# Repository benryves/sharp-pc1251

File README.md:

# Sharp PC-1251 & EC-125

This is a collection of example programs and tools for the Sharp PC-1251 and EC-125.

_**Disclaimer:** Except for the Audio Adapter, none of these files are my own. The original examples and documents are owned by Sharp and Pocket Tools is attributed below._

More information about this project can be found on my Retro website: [retro.engineer](https://retro.engineer/projects/2021-01-16_Sharp_PC-1251/)

## Audio-Adapter directory

This directory contains the designs for the audio adapter PCB which is for sale in my [Tindie shop](https://www.tindie.com/products/22618/). 

## Audio directory

This contains audio recordings of the original example programs provided on the EC-125 micro-cassette, as well as a Dutch game presumably made by a previous owner of my device.

These files can be played back to the PC-1251 using the EC-125 audio-in connection.

## Basic directory

These are the basic files converted from the above audio files using Pocket Tools (see below)

Files A09 and A11 encountered errors during decoding and might not be reliable.

## Manuals directory

User guides:

* Sharp PC-1250 user guide
* Sharp CE-125 user guide

Service guides:

* Sharp PC-1250 service manual
* Sharp CE-125 circuit diagrams (very minimal)

Related guides:

* Seiko MTP201 technical reference (Printer used in the CE-125)
* Sharp CE-126P service manual (contains the same printer as used in the CE-125)

## EC-125 modification

The EC-125 only has an audio input and no option for audio output. But since I don't own any other micro-cassette players I decided to make a temporary modification to allow me to capture the audio.

I soldered a wire to the amplifier IC. This is the positive output of the audio signal, I used the battery ground as ground without any issue:

## Pocket Tools for macOS.

These are MacOS X binaries for the Pocket Tools available on [https://www.peil-partner.de/ifhe.de/sharp](https://www.peil-partner.de/ifhe.de/sharp) compiled and tested on macOS Catalina

Original sources are also included

wav2bin
```
Usage: wav2bin [Options] SrcFile(.wav/tap/img) [DstFile(.typ)]
SrcFile           : WAVe file (PCM, normalized, recommended is mono 16-bit with
                    a minimum sample rate from 22050 Hz (PC-1500 only 11025 Hz)
                    to 48 kHz or original wave files made by Bin2Wav)
DstFile           : Destination file (BASIC-program text or Binary image file)
Options
-t, --type=TYPE   : Destination file type
                     bas  BASIC-program text file (default), sha  shc Transfile
                     img  Binary image file (BASIC program, machine code, data)
                     rsv  ReSerVe mode data (image),   tap  Emulator raw format
-p, --pc=NUMBER   : SHARP pocket computer, (for BASIC-program text,
                     is required for 1421, 1600 Mode 1, optionally for other)
-c, --cspeed=VALUE: Ratio of CPU frequency to original (use it with a modified
                     Pocket Computer, if speedup was switched on, 0.94 to 2.7)
-u, --utf8=TYPE   : Convert special characters (only for BASIC-program text)
                     no   to ASCII transcription with brackets [reversible]
                     (yes), BOM: to UTF-8,  2esc: Escape seq,  2dos: to DOS-US
                     2asc to ASCII transcription for later serial transfer
-w, --width=VALUE : Minimum width of line number (only for BASIC-program text)
  | VAL[:|;|,|.|!]   2 to 10 (default: 5_), indentation off: 0, =VAL; for (: )
-q, --quiet       : Quiet mode (No display output)    2nd use: -w space_level.
    --tap         : from emulator tap,  --img=OFFSET: Image (Src file no wave)
    --version     : Display version information  -e, --endmark : write end mark
    --help        : Display this, more:  --help=r:recoding FAQ, =l:level(debug)
```

bin2Wav

```
Usage: bin2wav [Options] SrcFile(.typ) [DstFile(.wav/tap)]
SrcFile          : Binary image file (usually created by BAS2IMG or WAV2BIN)
DstFile          : WAVe file (default: SrcFile.wav) or tap file
-t, --type=TYPE   : Source file type
                     img  BASIC-program binary image (default) txt Text modus
                     bin  Binary assembly program or data   st,shc Transfile PC
                     dat  Data variable blocks (binary data)   asc ASCII Data
                     rsv  ReSerVe data (binary image)          bas ASCII Source
-p, --pc=NUMBER   : Sharp pocket computer, currently available 1211, 1245, 1251
                     1261, 1350, 1360, 1401, 1403, 1421, 1450, 1460, 1475, 1600
                     E500, E220, G850, 1500QT, SuperTape and more, default:1500
-c, --cspeed=VALUE: Ratio of CPU frequency to original (use it with a modified
                     Pocket Computer with speedup switched on, 0.2 to 2.7)
-a, --addr=VALUE  : 1. Start address, needed for BIN type, 2. Entry address
                     0 to 65535 or 0xFFFF, E500:0xFFFFFF (dflt: Manual. 2. no)
-s, --sync=VALUE  : Synchronisation duration, expressed in seconds, 2. Space
                     0.5 to 9 (default: 0.5 or minimum for the PC and waveform)
-nNAME, --name=   : Sharp file name (7 characters max, 16 for the PC-1500, E:8)
                     (default: DstFile without extension, nor path)  Subst:[HH]
-q, --quiet       : Quiet mode (minimal display output)
    --tap         : Destination file: Emulator tap byte format (not wave file)
    --version     : Display version information  -e, --endmark : end mark incl.
    --help        : Display this information,  --help=l : show option screen
-l, --level=VALUE : Print debug traces, more options, see help option screen
```

bas2img
```
Usage: bas2img [Options] SrcFile [DstFile]
SrcFile         : BASIC-program text file
DstFile         : Binary image file (default: SrcFile.img or .asc)
Options:
-p, --pc=NUMBER : Sharp pocket computer, currently supported
                   1150, 1211, 1245, 1248, 1251, 1261, 1280, 1350, 1360, 1401
                   1402, 1403, 1421, 1425, 1430, 1445, 1450, 1460, 1475, 1500
                   1600, E220, G850 and more (default: 1500),
                    Only at E500 series must be used the commands 'TEXT'
                    and then 'BASIC' after the transfer of an img.
-k, --keywords=KeywordFile (for tokens of add-on hardware, max. use: 3 times)
-o, --codepoints=CodepointFile (code points def. file, maximum use: 2 times)
-t, --type=TYPE : destination file type (default: img),  asc,txt,asm,asm5,asm6
                  img  BASIC Program binary image with intermediate code
                  txt  TEXT mode image,  asc  ASCII file: Text Menu Cmt/serial
-e, --endmark   : Append an end mark to the file,     -u, --utf8= (yes),no,dos
-q, --quiet     : Quiet mode (minimal display output) -a, --auto= AUTO_inc(10)
    --version   : Display version information --help: Display this information
-l, --level=SUM : 1     Don't/Do compile fixed line no. (in line) =0x1000:ELbl
   (max use 2x) : 2     Append missing apostrophes at end of line =0x2000: Bgn
                : 4     Don't replace shortcuts(.) with commands, =0x100: SJIS
                : 8     Don't convert to upper case, 0x10 Disable preprocessor
                : 0x80 (0x20) Print lines in,        0x40 Print values out
                : 0x800 Depress some line errors, result may not editable
```

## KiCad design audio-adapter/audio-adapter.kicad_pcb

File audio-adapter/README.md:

# Sharp PC-1251 audio adapter

The Sharp PC-1251 / TRS-80 PC1 audio connector lets you load and safe programs directly to a computer or phone.

It's easy to use and doesn't require a EC-125 or similar.

Most likely it also works with other 11-pin sharp models, but I haven't been able to test that yet.

This product is released under the [Creative Commons Attribution 4.0 License](http://creativecommons.org/licenses/by/4.0/)

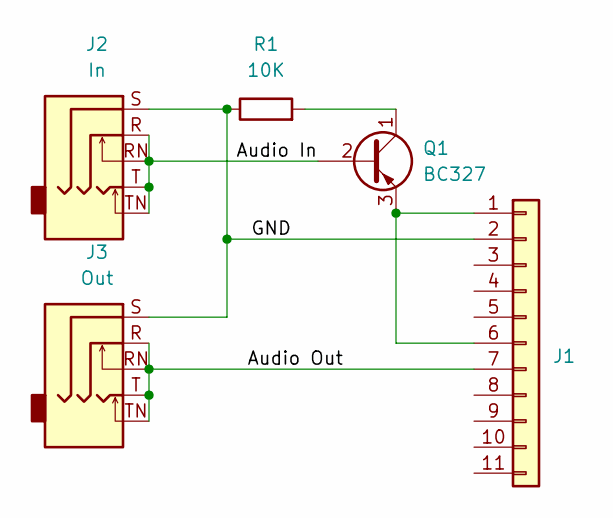
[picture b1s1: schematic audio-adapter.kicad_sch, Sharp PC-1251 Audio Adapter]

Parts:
J1: Conn_01x11; PinHeader_1x11_P2.54mm_Vertical
J2: In; Jack_3.5mm_CUI_SJ1-3535NG_Horizontal
J3: Out; Jack_3.5mm_CUI_SJ1-3535NG_Horizontal
Q1: BC327; TO-92_Inline
R1: 10K; R_Axial_DIN0204_L3.6mm_D1.6mm_P7.62mm_Horizontal

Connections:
/Audio In: J2.R, J2.RN, J2.T, J2.TN, Q1.2 (B)
/Audio Out: J1.7, J3.R, J3.RN, J3.T, J3.TN
/GND: J1.2, J2.S, J3.S, R1.1
unnamed: J1.1, J1.6, Q1.3 (E)
unnamed: Q1.1 (C), R1.2

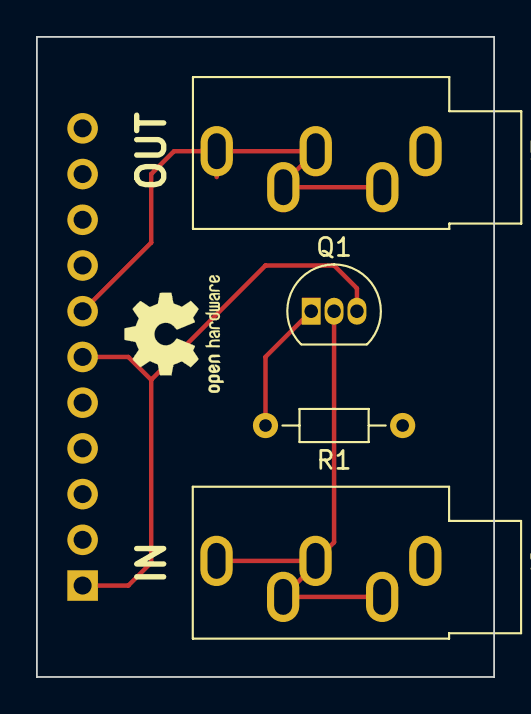
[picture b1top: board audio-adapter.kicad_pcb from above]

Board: 2 copper layers, 25.4 x 35.6 mm, 5 parts (0 on the bottom side), 5 nets.

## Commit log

2021-01-29 Small fixes
2021-02-28 audio-adapter
2021-03-01 Minor fixes
2023-08-15 Clean-up
2025-06-17 Re-converted BASIC programs to fix errors.
    Source wave file recordings were cleaned up with a 5kHz low-pass filter then normalised before running through wav2bin. No errors were reported in the conversion after doing this, whereas previously 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

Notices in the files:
audio-adapter/audio-adapter.kicad_pcb:
License: Creative Commons Attribution 4.0
